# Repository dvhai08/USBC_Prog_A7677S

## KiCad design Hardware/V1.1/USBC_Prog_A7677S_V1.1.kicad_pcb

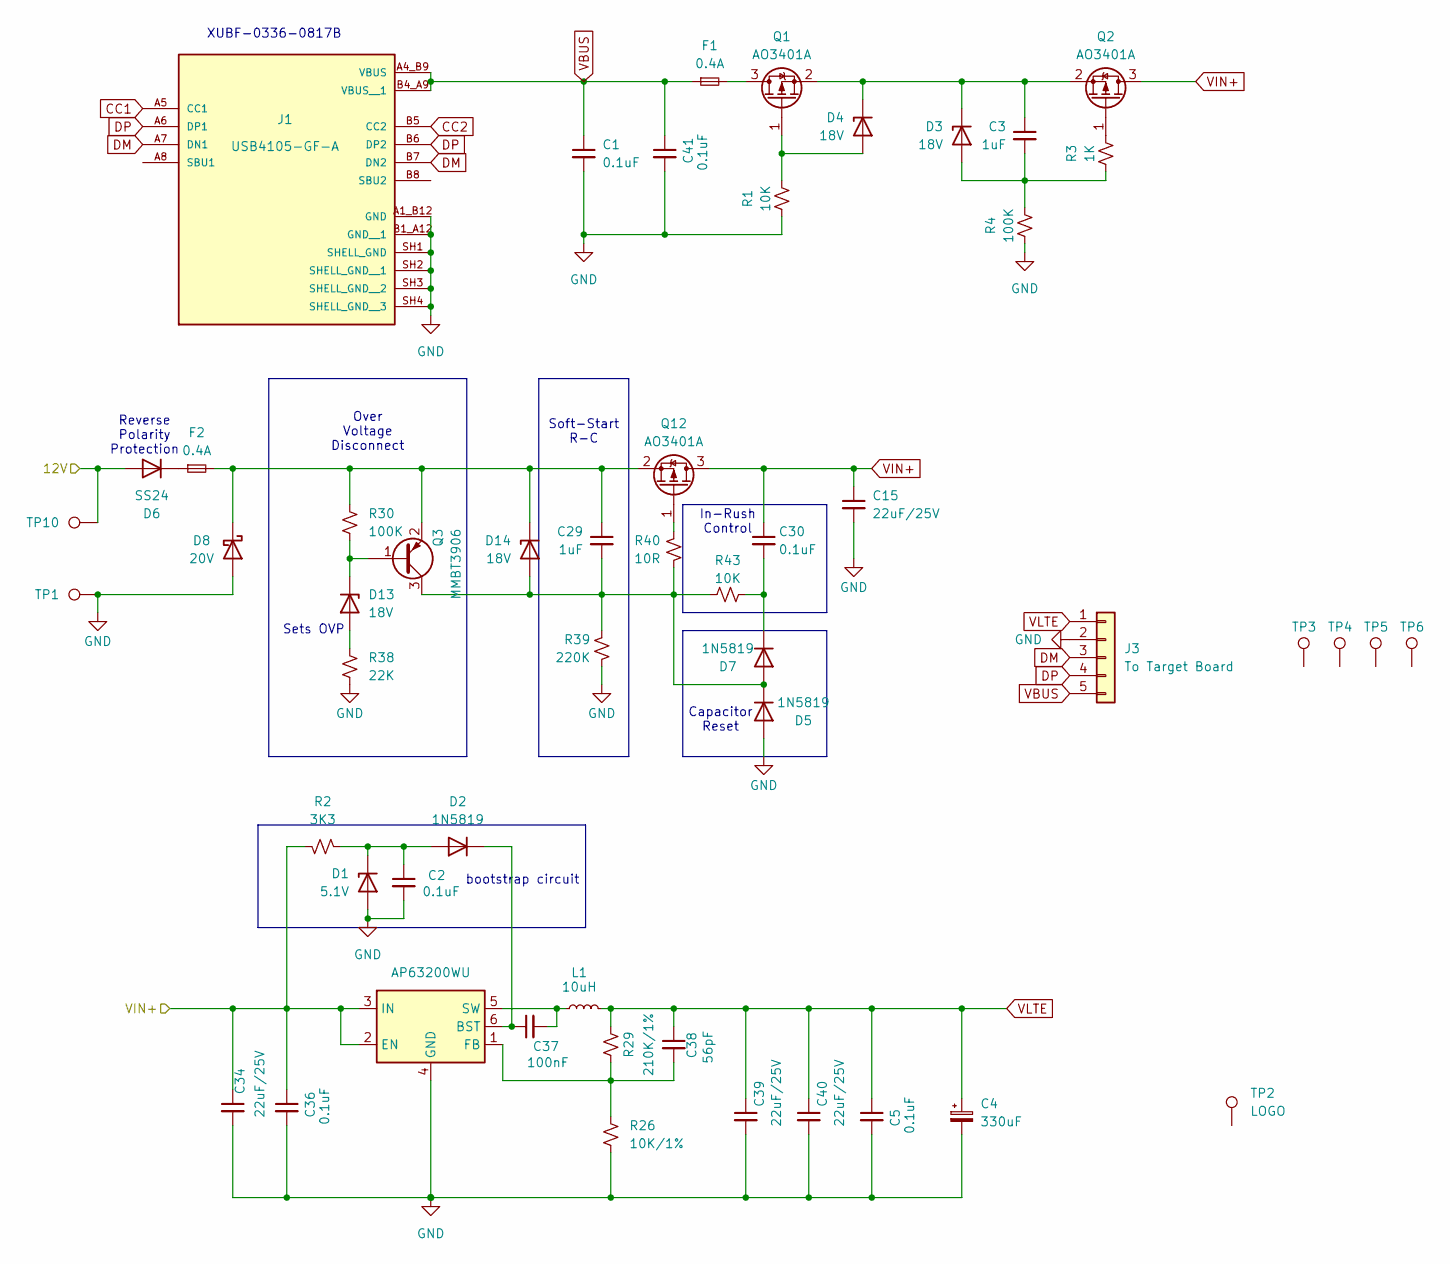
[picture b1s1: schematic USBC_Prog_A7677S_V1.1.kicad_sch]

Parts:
C1, C2, C5, C30, C41: 0.1uF; C_0603_1608Metric
C3, C29: 1uF; C_0603_1608Metric
C4: 330uF; CP_EIA-7343-40_Kemet-Y_Pad2.25x2.55mm_HandSolder
C15, C39, C40: 22uF/25V; C_0805_2012Metric
C34: 22uF/25V; C_0805_2012Metric; Manufacturer P/N CL21A226MAYNNNE
C36: 0.1uF; C_0402_1005Metric
C37: 100nF; C_0402_1005Metric; Manufacturer P/N CL05B104KB5NNNC
C38: 56pF; C_0402_1005Metric; Manufacturer P/N CL05B104KB5NNNC
D1: 5.1V; D_SOD-323_HandSoldering
D2, D5, D7: 1N5819; D_SOD-123
D3, D4, D13, D14: 18V; D_SOD-323_HandSoldering
D6: SS24; D_SMB
D8: 20V; D_SMB; Manufacturer P/N SMAJ20CA
F1, F2: 0.4A; Fuse_1206_3216Metric
J1: USB4105-GF-A; GCT_USB4105-GF-A; PARTREV B4
J3: To Target Board; PinHeader_1x05_P2.54mm_Vertical
L1: 10uH; L_Sunlord_SWPA6028S; Manufacturer P/N NRS8030T100MJGJ
Q1, Q2, Q12: AO3401A; SOT-23
Q3: MMBT3906; SOT-23
R1, R43: 10K; R_0603_1608Metric
R2: 3K3; R_0603_1608Metric
R3: 1K; R_0603_1608Metric
R4, R30: 100K; R_0603_1608Metric
R26: 10K/1%; R_0402_1005Metric; Manufacturer P/N RC0402FR-0715KL
R29: 210K/1%; R_0402_1005Metric; Manufacturer P/N RC0402FR-07210KL
R38: 22K; R_0603_1608Metric
R39: 220K; R_0603_1608Metric
R40: 10R; R_0603_1608Metric
TP1: GND; TestPoint_Pad_D4.0mm
TP2: LOGO; LoGo12mm_NoText
TP3, TP4, TP5, TP6: TestPoint; MountingHole_3mm_Pad
TP10: VIN; TestPoint_Pad_D4.0mm
U3: AP63200WU; TSOT-23-6

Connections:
/12V: D6.2 (A), TP10.1
CC1: J1.A5 (CC1)
CC2: J1.B5 (CC2)
DM: J1.A7 (DN1), J1.B7 (DN2), J3.3
DP: J1.A6 (DP1), J1.B6 (DP2), J3.4
GND: C1.2, C2.2, C4.2, C5.2, C15.2, C34.2, C36.2, C39.2, C40.2, C41.2, D1.2 (A), D5.2 (A), D8.2 (A), J1.A1_B12 (GND), J1.B1_A12 (GND__1), J1.SH1 (SHELL_GND), J1.SH2 (SHELL_GND__1), J1.SH3 (SHELL_GND__2), J1.SH4 (SHELL_GND__3), J3.2, R1.2, R4.2, R26.2, R38.1, R39.1, TP1.1, U3.4 (GND)
unnamed: C2.1, D1.1 (K), D2.2 (A), R2.1
unnamed: C37.1, D2.1 (K), U3.6 (BST)
unnamed: C3.2, D3.2 (A), R3.2, R4.1
unnamed: C3.1, D3.1 (K), D4.1 (K), Q1.2 (S), Q2.2 (S)
unnamed: D4.2 (A), Q1.1 (G), R1.1
unnamed: D6.1 (K), F2.1
unnamed: C30.2, D7.1 (K), R43.1
unnamed: D13.2 (A), R38.2
unnamed: D13.1 (K), Q3.1 (B), R30.2
unnamed: C29.2, D5.1 (K), D7.2 (A), D14.2 (A), Q3.3 (C), R39.2, R40.1, R43.2
unnamed: C29.1, D8.1 (K), D14.1 (K), F2.2, Q3.2 (E), Q12.2 (S), R30.1
unnamed: F1.2, Q1.3 (D)
unnamed: Q2.1 (G), R3.1
unnamed: Q12.1 (G), R40.2
unnamed: C38.2, R26.1, R29.2, U3.1 (FB)
unnamed: C37.2, L1.2, U3.5 (SW)
VBUS: C1.1, C41.1, F1.1, J1.A4_B9 (VBUS), J1.B4_A9 (VBUS__1), J3.5
VIN+: C15.1, C30.1, C34.1, C36.1, Q2.3 (D), Q12.3 (D), R2.2, U3.2 (EN), U3.3 (IN)
VLTE: C4.1, C5.1, C38.1, C39.1, C40.1, J3.1, L1.1, R29.1

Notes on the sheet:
Sets OVP
Capacitor Reset
Soft-Start R-C
bootstrap circuit
Reverse Polarity Protection
XUBF-0336-0817B
Over Voltage Disconnect
In-Rush Control

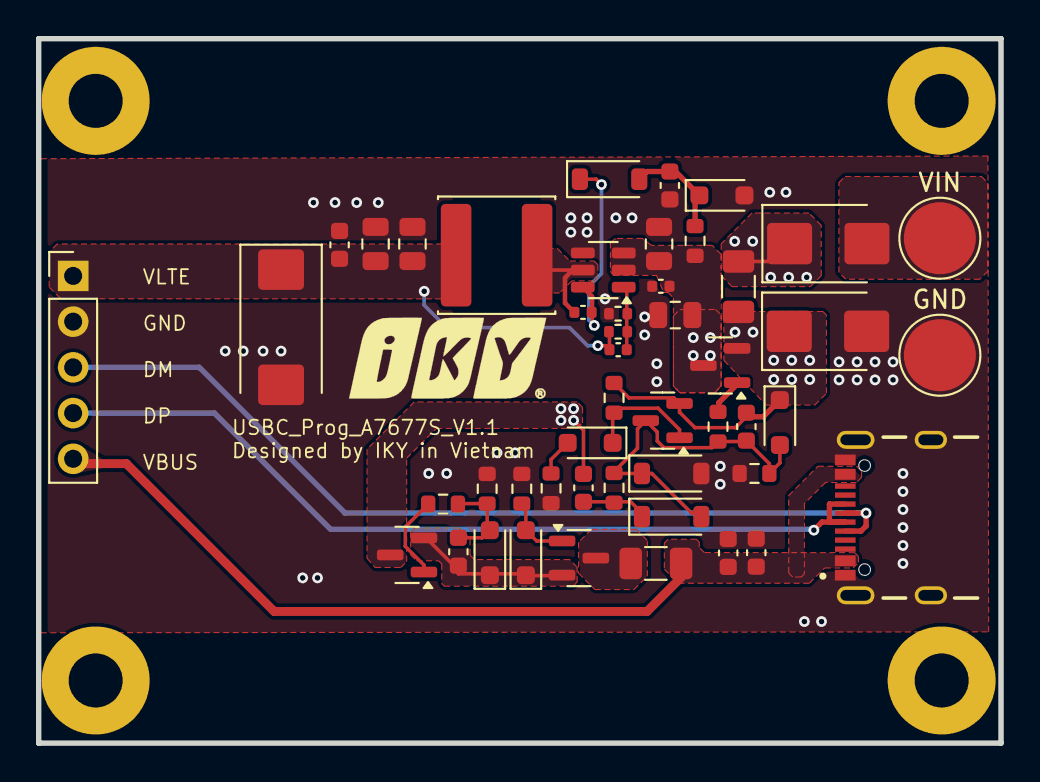
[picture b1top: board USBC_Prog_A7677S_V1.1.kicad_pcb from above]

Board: 2 copper layers, 53.5 x 39.1 mm, 53 parts (0 on the bottom side), 23 nets.

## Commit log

2025-07-16 add readme
